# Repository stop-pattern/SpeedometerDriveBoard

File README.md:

SpeedometerDriveBoard
===

## table of contents
- [日本語版](#Japanese)
- [English](#English)
  - [Requirement](#Requirement)
  - [Installation](#Installation)
    - [board](#board)
    - [code](#code)
  - [Licence](#Licence)
  - [Author](#Author)

---

## Japanese
このリポジトリ内の創造物は、[BIDSid_SerCon](https://github.com/TetsuOtter/BIDSid_SerCon/)を使用する前提で設計されています。  
基板は5000円以下/枚で生産できますが、現在製造中につき値段の詳細については分かりかねます。(分かり次第追記予定  
日本語版は工事中ですのでお手数ですが下記英語版をご覧いただきますよう...

---

## English
This Repository is designed on the premise of using [__BIDSid_SerCon__](https://github.com/TetsuOtter/BIDSid_SerCon/).  
This is for original board on esp32 that created and designed by stop_pattern.  
This board can be produced at less than 5000JPY / piece.  
But do not know details of the price because it is currently under manufacturing.  
(Scheduled to be appended as soon as it is known)  

### Requirement
using:
[BIDSid_SerCon](https://github.com/TetsuOtter/BIDSid_SerCon/).  
supported:
[Bve trainsim](http://bvets.net/)  
support __Bve trainsim__, but the supported version _5.7_ or newer.  
__Bve trainsim__ spported only _Windows Vista_ or _newer_, so support only _Windows Vista_ or _newer_ too.  

### Usage
Change the settings, in the firmware source code according to your own environment.  
write firmware to esp32 through __Arduino IDE__.  

### Installation
#### board:
1. Request PCB service company to manufacture circuit board.  
2. Test manufactured board and Implemented parts.  
#### code:
1. write firmware to esp32 through __Arduino IDE__.  
2. setup [__Bve trainsim__](http://bvets.net/en/download/)  
3. Introduce [__BIDSid_SerCon__](https://github.com/TetsuOtter/BIDSid_SerCon/) into __Bve trainsim__.  

### Licence
board:
[GPLv3](https://www.gnu.org/licenses/gpl-3.0.html)  
code:
[MIT](https://github.com/tcnksm/tool/blob/master/LICENCE)  

### Author
[stop_pattern](https://github.com/stop-pattern)

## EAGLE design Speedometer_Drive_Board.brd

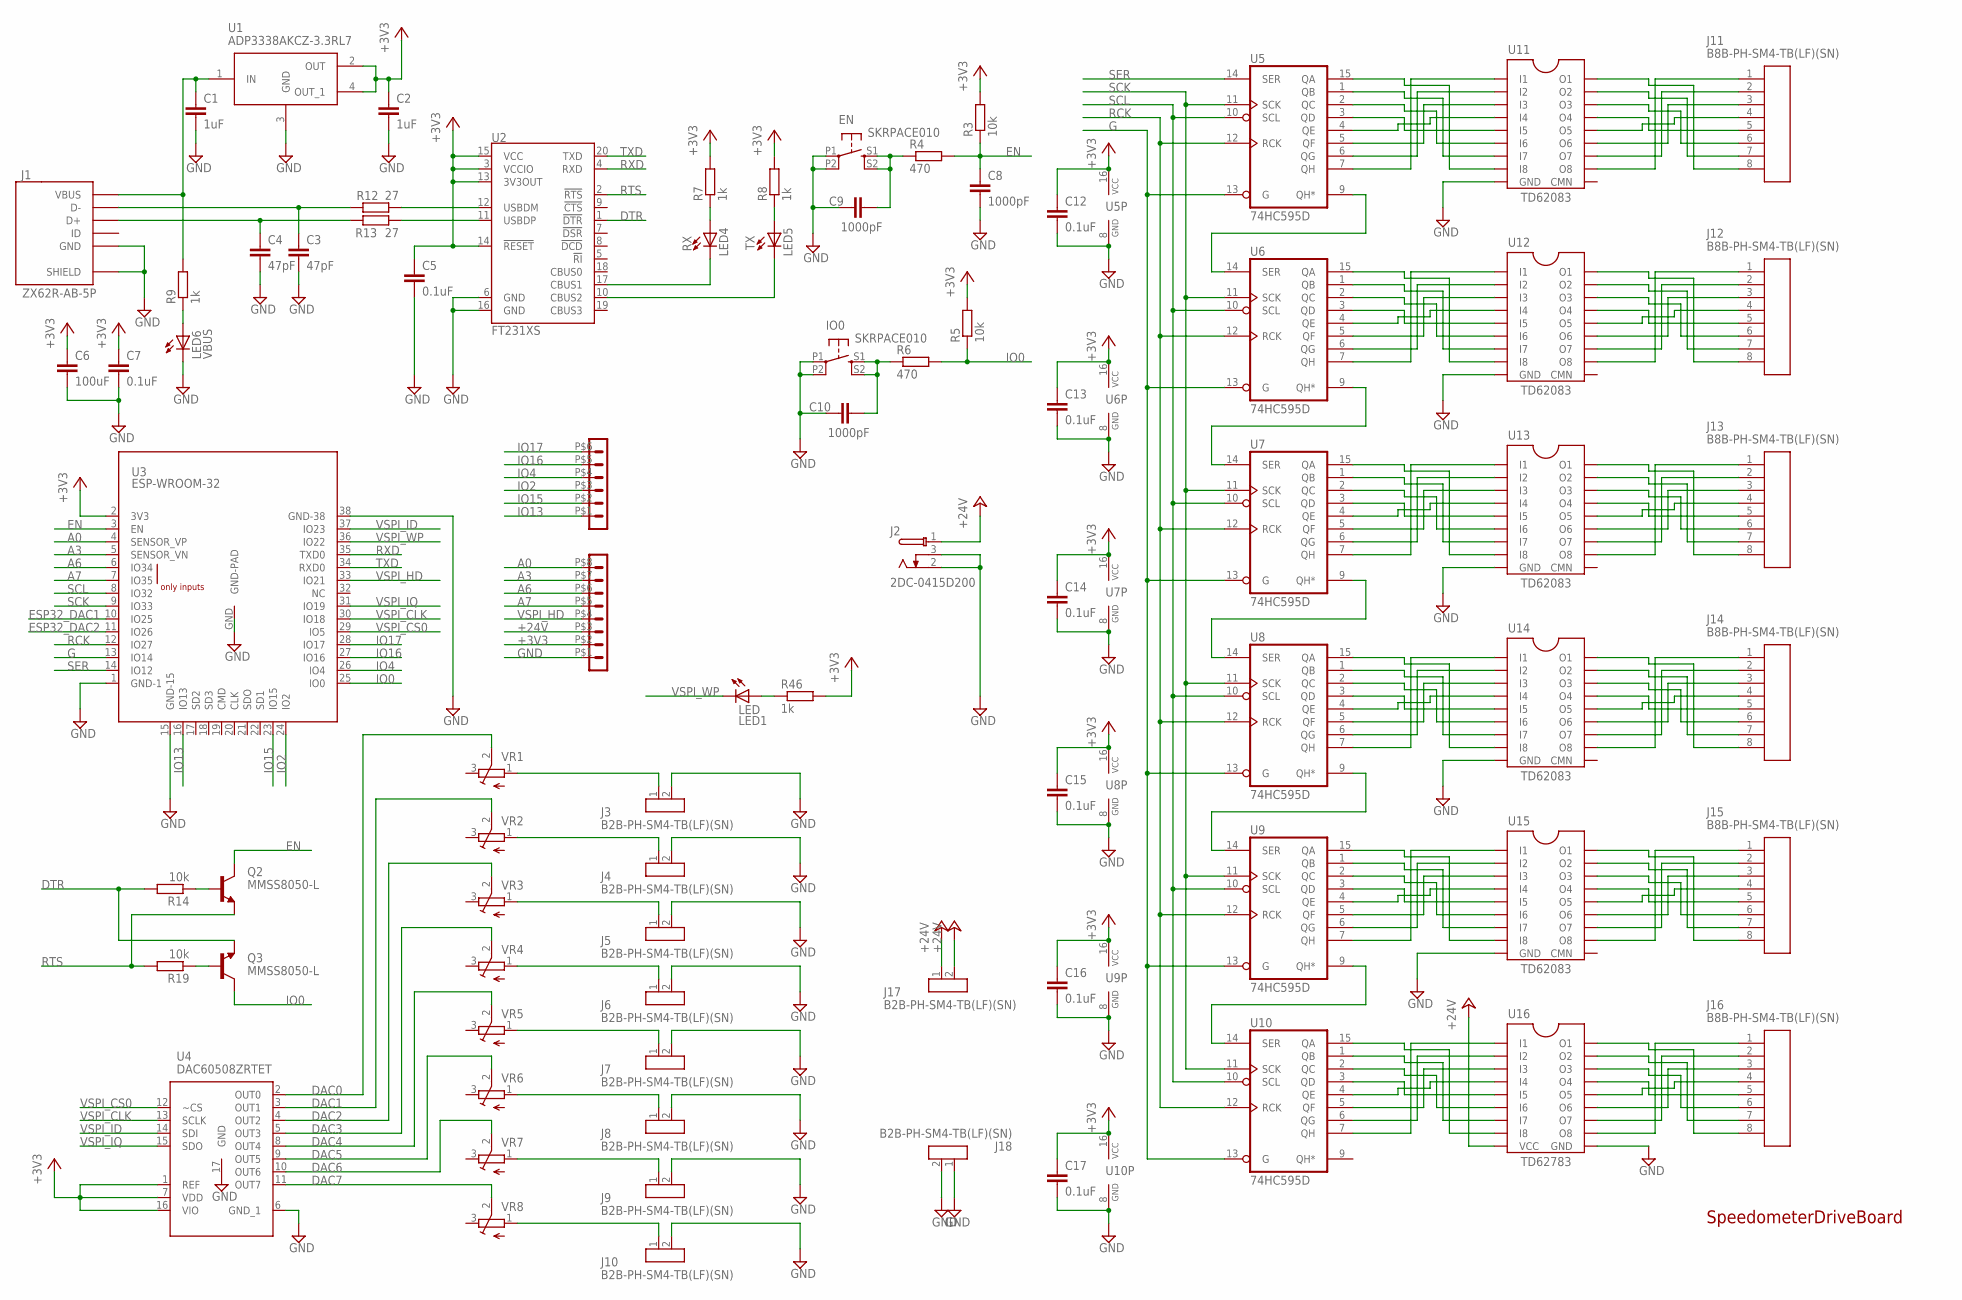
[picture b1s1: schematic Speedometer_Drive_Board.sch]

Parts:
C1, C2: 1uF; C0603
C3, C4: 47pF; C0603
C5, C7, C12, C13, C14, C15, C16, C17: 0.1uF; C0603
C6: 100uF; C1210
C8, C9, C10: 1000pF; C0603
EN: SKRPACE010
IO0: SKRPACE010
J1: ZX62R-AB-5P; ZX62R-B-5PA
J2: 2DC-0415D200
J3, J4, J5, J6, J7, J8, J9, J10, J17, J18: B2B-PH-SM4-TB(LF)(SN); SAMACSYS_PARTS_B2B-PH-SM4-TB
J11, J12, J13, J14, J15, J16: B8B-PH-SM4-TB(LF)(SN); SAMACSYS_PARTS_B8B-PH-SM4-TB
J19: PIN_HEADER_MALE_1X06_06P
J20: PIN_HEADER_MALE_1X08_08P
LED: LED1; CHIPLED_0603
LED4: RX; CHIPLED_0603
LED5: TX; CHIPLED_0603
LED6: VBUS; CHIPLED_0603
Q2, Q3: MMSS8050-L; SOT23
R3, R5, R14, R19: 10k; R0603
R4, R6: 470; R0603
R7, R8, R9, R46: 1k; R0603
R12, R13: 27; R0603
U1: ADP3338AKCZ-3.3RL7; SOT230P700X180-4N
U2: FT231XS; SSOP20_L
U3: ESP-WROOM-32
U4: DAC60508ZRTET; SAMACSYS_PARTS_QFN50P300X300X80-17N
U5, U6, U7, U8, U9, U10: 74HC595D; SO16
U11, U12, U13, U14, U15: TD62083; SO18
U16: TD62783; SO18
VR1, VR2, VR3, VR4, VR5, VR6, VR7, VR8: TRIM_EU-SM-42/43W; SM-42/43W

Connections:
+3V3: C2.1, C5.1, C6.1, C7.1, C12.1, C13.1, C14.1, C15.1, C16.1, C17.1, J20.P$2 (2), R3.2, R5.2, R7.2, R8.2, R46.2, U1.2 (OUT), U1.4 (OUT_1), U2.3 (VCCIO), U2.13 (3V3OUT), U2.14 (!RESET), U2.15 (VCC), U3.2 (3V3), U4.1 (REF), U4.7 (VDD), U4.16 (VIO), U5.16 (VCC), U6.16 (VCC), U7.16 (VCC), U8.16 (VCC), U9.16 (VCC), U10.16 (VCC)
+24V: J2.1, J17.1, J17.2, J20.P$3 (3), U16.9 (VCC)
A0: J20.P$8 (8), U3.4 (SENSOR_VP)
A3: J20.P$7 (7), U3.5 (SENSOR_VN)
A6: J20.P$6 (6), U3.6 (IO34)
A7: J20.P$5 (5), U3.7 (IO35)
D2_N1: R12.2, U2.12 (USBDM)
D2_P1: R13.2, U2.11 (USBDP)
DAC0: U4.2 (OUT0), VR1.2 (S)
DAC1: U4.3 (OUT1), VR2.2 (S)
DAC2: U4.4 (OUT2), VR3.2 (S)
DAC3: U4.5 (OUT3), VR4.2 (S)
DAC4: U4.8 (OUT4), VR5.2 (S)
DAC5: U4.9 (OUT5), VR6.2 (S)
DAC6: U4.10 (OUT6), VR7.2 (S)
DAC7: U4.11 (OUT7), VR8.2 (S)
DTR: Q3.E, R14.2, U2.1 (!DTR)
D_N1: C3.1, J1.D-, R12.1
D_P1: C4.1, J1.D+, R13.1
EN: C8.1, Q2.C, R3.1, R4.2, U3.3 (EN)
ESP32_DAC1: U3.10 (IO25)
ESP32_DAC2: U3.11 (IO26)
G: U3.13 (IO14), U5.13 (G), U6.13 (G), U7.13 (G), U8.13 (G), U9.13 (G), U10.13 (G)
GND: C1.2, C2.2, C3.2, C4.2, C5.2, C6.2, C7.2, C8.2, C9.1, C10.1, C12.2, C13.2, C14.2, C15.2, C16.2, C17.2, EN.P1, EN.P2 (P1), IO0.P1, IO0.P2 (P1), J1.GND, J1.SHIELD@1 (SHIELD), J1.SHIELD@2 (SHIELD), J1.SHIELD@3 (SHIELD), J1.SHIELD@4 (SHIELD), J2.2, J2.3, J3.2, J4.2, J5.2, J6.2, J7.2, J8.2, J9.2, J10.2, J18.1, J18.2, J20.P$1 (1), LED6.C, U1.3 (GND), U2.6 (GND), U2.16 (GND), U3.1 (GND-1), U3.15 (GND-15), U3.38 (GND-38), U3.GND (GND-PAD), U4.6 (GND_1), U4.17 (GND), U5.8 (GND), U6.8 (GND), U7.8 (GND), U8.8 (GND), U9.8 (GND), U10.8 (GND), U11.9 (GND), U12.9 (GND), U13.9 (GND), U14.9 (GND), U15.9 (GND), U16.10 (GND)
IO0: Q3.C, R5.1, R6.2, U3.25 (IO0)
IO2: J19.P$3 (3), U3.24 (IO2)
IO4: J19.P$4 (4), U3.26 (IO4)
IO13: J19.P$1 (1), U3.16 (IO13)
IO15: J19.P$2 (2), U3.23 (IO15)
IO16: J19.P$5 (5), U3.27 (IO16)
IO17: J19.P$6 (6), U3.28 (IO17)
unnamed: U5.9 (QH*), U6.14 (SER)
unnamed: U6.9 (QH*), U7.14 (SER)
unnamed: U7.9 (QH*), U8.14 (SER)
unnamed: U5.7 (QH), U11.1 (I1)
unnamed: U5.6 (QG), U11.2 (I2)
unnamed: U5.5 (QF), U11.3 (I3)
unnamed: LED.A, R46.1
unnamed: U5.4 (QE), U11.4 (I4)
unnamed: U5.3 (QD), U11.5 (I5)
unnamed: U5.2 (QC), U11.6 (I6)
unnamed: U5.1 (QB), U11.7 (I7)
unnamed: U5.15 (QA), U11.8 (I8)
unnamed: J11.1 (S1), U11.11 (O8)
unnamed: J11.2 (S2), U11.12 (O7)
unnamed: J11.3 (S3), U11.13 (O6)
unnamed: J11.4 (S4), U11.14 (O5)
unnamed: J11.5 (S5), U11.15 (O4)
unnamed: J11.6 (S6), U11.16 (O3)
unnamed: J11.7 (S7), U11.17 (O2)
unnamed: J11.8 (S8), U11.18 (O1)
unnamed: U7.7 (QH), U13.1 (I1)
unnamed: U6.7 (QH), U12.1 (I1)
unnamed: U6.6 (QG), U12.2 (I2)
unnamed: U6.5 (QF), U12.3 (I3)
unnamed: U6.4 (QE), U12.4 (I4)
unnamed: U6.3 (QD), U12.5 (I5)
unnamed: U6.2 (QC), U12.6 (I6)
unnamed: U6.1 (QB), U12.7 (I7)
unnamed: U6.15 (QA), U12.8 (I8)
unnamed: J12.1 (S1), U12.11 (O8)
unnamed: J12.2 (S2), U12.12 (O7)
unnamed: J12.3 (S3), U12.13 (O6)
unnamed: J12.4 (S4), U12.14 (O5)
unnamed: J12.5 (S5), U12.15 (O4)
unnamed: J12.6 (S6), U12.16 (O3)
unnamed: J12.7 (S7), U12.17 (O2)
unnamed: J12.8 (S8), U12.18 (O1)
unnamed: U7.6 (QG), U13.2 (I2)
unnamed: U7.5 (QF), U13.3 (I3)
unnamed: U7.4 (QE), U13.4 (I4)
unnamed: U7.3 (QD), U13.5 (I5)
unnamed: U7.2 (QC), U13.6 (I6)
unnamed: U7.1 (QB), U13.7 (I7)
unnamed: U7.15 (QA), U13.8 (I8)
unnamed: J13.1 (S1), U13.11 (O8)
unnamed: J13.2 (S2), U13.12 (O7)
unnamed: J13.3 (S3), U13.13 (O6)
unnamed: J13.4 (S4), U13.14 (O5)
unnamed: J13.5 (S5), U13.15 (O4)
unnamed: J13.6 (S6), U13.16 (O3)
unnamed: J13.7 (S7), U13.17 (O2)
unnamed: J13.8 (S8), U13.18 (O1)
unnamed: U8.7 (QH), U14.1 (I1)
unnamed: U8.6 (QG), U14.2 (I2)
unnamed: U8.5 (QF), U14.3 (I3)
unnamed: U8.4 (QE), U14.4 (I4)
unnamed: U8.3 (QD), U14.5 (I5)
unnamed: U8.2 (QC), U14.6 (I6)
unnamed: U8.1 (QB), U14.7 (I7)
unnamed: U8.15 (QA), U14.8 (I8)
unnamed: J14.1 (S1), U14.11 (O8)
unnamed: J14.2 (S2), U14.12 (O7)
unnamed: J14.3 (S3), U14.13 (O6)
unnamed: J14.4 (S4), U14.14 (O5)
unnamed: J14.5 (S5), U14.15 (O4)
unnamed: J14.6 (S6), U14.16 (O3)
unnamed: J14.7 (S7), U14.17 (O2)
unnamed: J14.8 (S8), U14.18 (O1)
unnamed: U9.7 (QH), U15.1 (I1)
unnamed: U9.6 (QG), U15.2 (I2)
unnamed: U9.5 (QF), U15.3 (I3)
unnamed: U9.4 (QE), U15.4 (I4)
unnamed: U9.3 (QD), U15.5 (I5)
unnamed: U9.2 (QC), U15.6 (I6)
unnamed: U8.9 (QH*), U9.14 (SER)
unnamed: U9.1 (QB), U15.7 (I7)
unnamed: U9.15 (QA), U15.8 (I8)
unnamed: J15.1 (S1), U15.11 (O8)
unnamed: J15.2 (S2), U15.12 (O7)
unnamed: J15.3 (S3), U15.13 (O6)
unnamed: J15.4 (S4), U15.14 (O5)
unnamed: J15.5 (S5), U15.15 (O4)
unnamed: J15.6 (S6), U15.16 (O3)
unnamed: J15.7 (S7), U15.17 (O2)
unnamed: J15.8 (S8), U15.18 (O1)
unnamed: U10.7 (QH), U16.1 (I1)
unnamed: U10.6 (QG), U16.2 (I2)
unnamed: U10.5 (QF), U16.3 (I3)
unnamed: U10.4 (QE), U16.4 (I4)
unnamed: U10.3 (QD), U16.5 (I5)
unnamed: U10.2 (QC), U16.6 (I6)
unnamed: U10.1 (QB), U16.7 (I7)
unnamed: U9.9 (QH*), U10.14 (SER)
unnamed: U10.15 (QA), U16.8 (I8)
unnamed: J16.1 (S1), U16.11 (O8)
unnamed: J16.2 (S2), U16.12 (O7)
unnamed: J16.3 (S3), U16.13 (O6)
unnamed: J16.4 (S4), U16.14 (O5)
unnamed: J16.5 (S5), U16.15 (O4)
unnamed: J16.6 (S6), U16.16 (O3)
unnamed: J16.7 (S7), U16.17 (O2)
unnamed: J16.8 (S8), U16.18 (O1)
unnamed: J10.1, VR8.1 (A)
unnamed: J9.1, VR7.1 (A)
unnamed: J8.1, VR6.1 (A)
unnamed: J7.1, VR5.1 (A)
unnamed: J3.1, VR1.1 (A)
unnamed: J4.1, VR2.1 (A)
unnamed: J5.1, VR3.1 (A)
unnamed: J6.1, VR4.1 (A)
unnamed: C9.2, EN.S1 (S), EN.S2 (S1), R4.1
unnamed: C10.2, IO0.S1 (S), IO0.S2 (S1), R6.1
unnamed: LED4.C, U2.17 (CBUS1)
unnamed: LED5.C, U2.10 (CBUS2)
unnamed: LED4.A, R7.1
unnamed: LED5.A, R8.1
unnamed: LED6.A, R9.1
unnamed: Q2.B, R14.1
unnamed: Q3.B, R19.1
RCK: U3.12 (IO27), U5.12 (RCK), U6.12 (RCK), U7.12 (RCK), U8.12 (RCK), U9.12 (RCK), U10.12 (RCK)
RTS: Q2.E, R19.2, U2.2 (!RTS)
RXD: U2.4 (RXD), U3.35 (TXD0)
SCK: U3.9 (IO33), U5.11 (SCK), U6.11 (SCK), U7.11 (SCK), U8.11 (SCK), U9.11 (SCK), U10.11 (SCK)
SCL: U3.8 (IO32), U5.10 (SCL), U6.10 (SCL), U7.10 (SCL), U8.10 (SCL), U9.10 (SCL), U10.10 (SCL)
SER: U3.14 (IO12), U5.14 (SER)
TXD: U2.20 (TXD), U3.34 (RXD0)
VBUS3: C1.1, J1.VCC (VBUS), R9.2, U1.1 (IN)
VSPI_CLK: U3.30 (IO18), U4.13 (SCLK)
VSPI_CS0: U3.29 (IO5), U4.12 (~CS)
VSPI_HD: J20.P$4 (4), U3.33 (IO21)
VSPI_ID: U3.37 (IO23), U4.14 (SDI)
VSPI_IQ: U3.31 (IO19), U4.15 (SDO)
VSPI_WP: LED.C, U3.36 (IO22)

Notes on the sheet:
SpeedometerDriveBoard

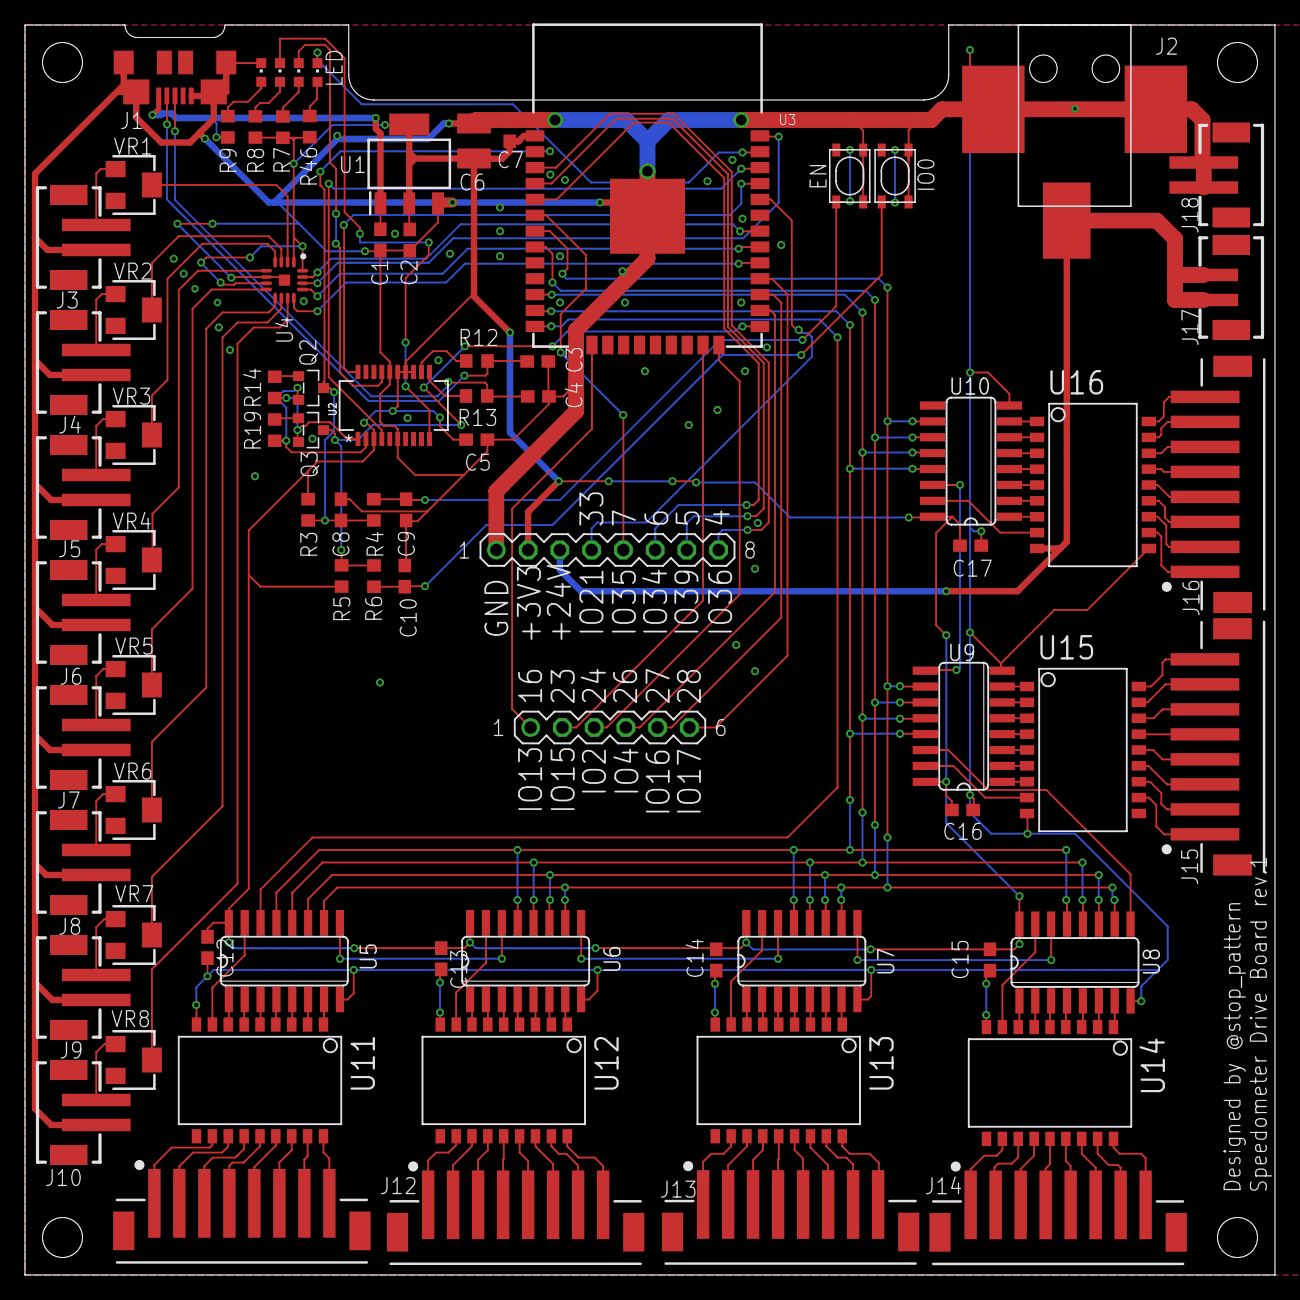
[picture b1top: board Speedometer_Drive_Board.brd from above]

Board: 2 copper layers, 100.0 x 100.0 mm, 80 parts (0 on the bottom side), 162 nets.

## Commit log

2018-11-30 [add] add readme
2018-11-30 [update] update readme
2018-11-30 [add] add Schematic & Board
2018-12-09 [update] update readme.md
2019-01-17 [clean] フォルダ整理
2019-01-17 [add] コード追加
    基板用ファームコード追加
2019-01-18 [add] コードを追加
    firm/ 基板ファーム (途中）
    firm_test/ 速度計Lチカ （動かない）
    test_LED/ 基板上Lチカ （完成）
2019-01-18 [fix] 基板Lチカコードのミスを修正
2019-02-22 add LCENSE
2019-02-23 update firmware
2019-02-23 動いたやつ
2019-02-24 デモ仕様
2019-02-24 bell改良&通信回数削減
2019-04-04 [change] 色々変えたのでなに変えたか覚えてない
    ボタン操作で割込みから警笛ならせるようにはした
    通信回数がどうしても多いのでプラグイン書いてpanelを一か所潰してその値を丸ごと送受信するようにしたいかなぁと模索中
    次までにこれよりいい案がなければ多分これで実装する
2019-04-11 [update] update firmware
    ifdef _NEW_ で[board_PI](https://github.com/stop-pattern/board_PI)に対応
    なお旧版はelseで使用可能
2019-04-13 [fix] fix transmission bug
    modified to change the state of chip select pin
